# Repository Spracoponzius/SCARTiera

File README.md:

# SCARTiera
Mechanical multiSCART adapter with 6 positions.  

Due to a lack of options of multi-scart adapters ready to buy (always either out of stock, with only three positions or too expensive), i made one myself by reverse engineering a simpler three-positions adapter.  
This is a hobby project, and contributions, suggestions, and feedback are all very welcome.  
This design is currently **untested**, so build this at your own risk.

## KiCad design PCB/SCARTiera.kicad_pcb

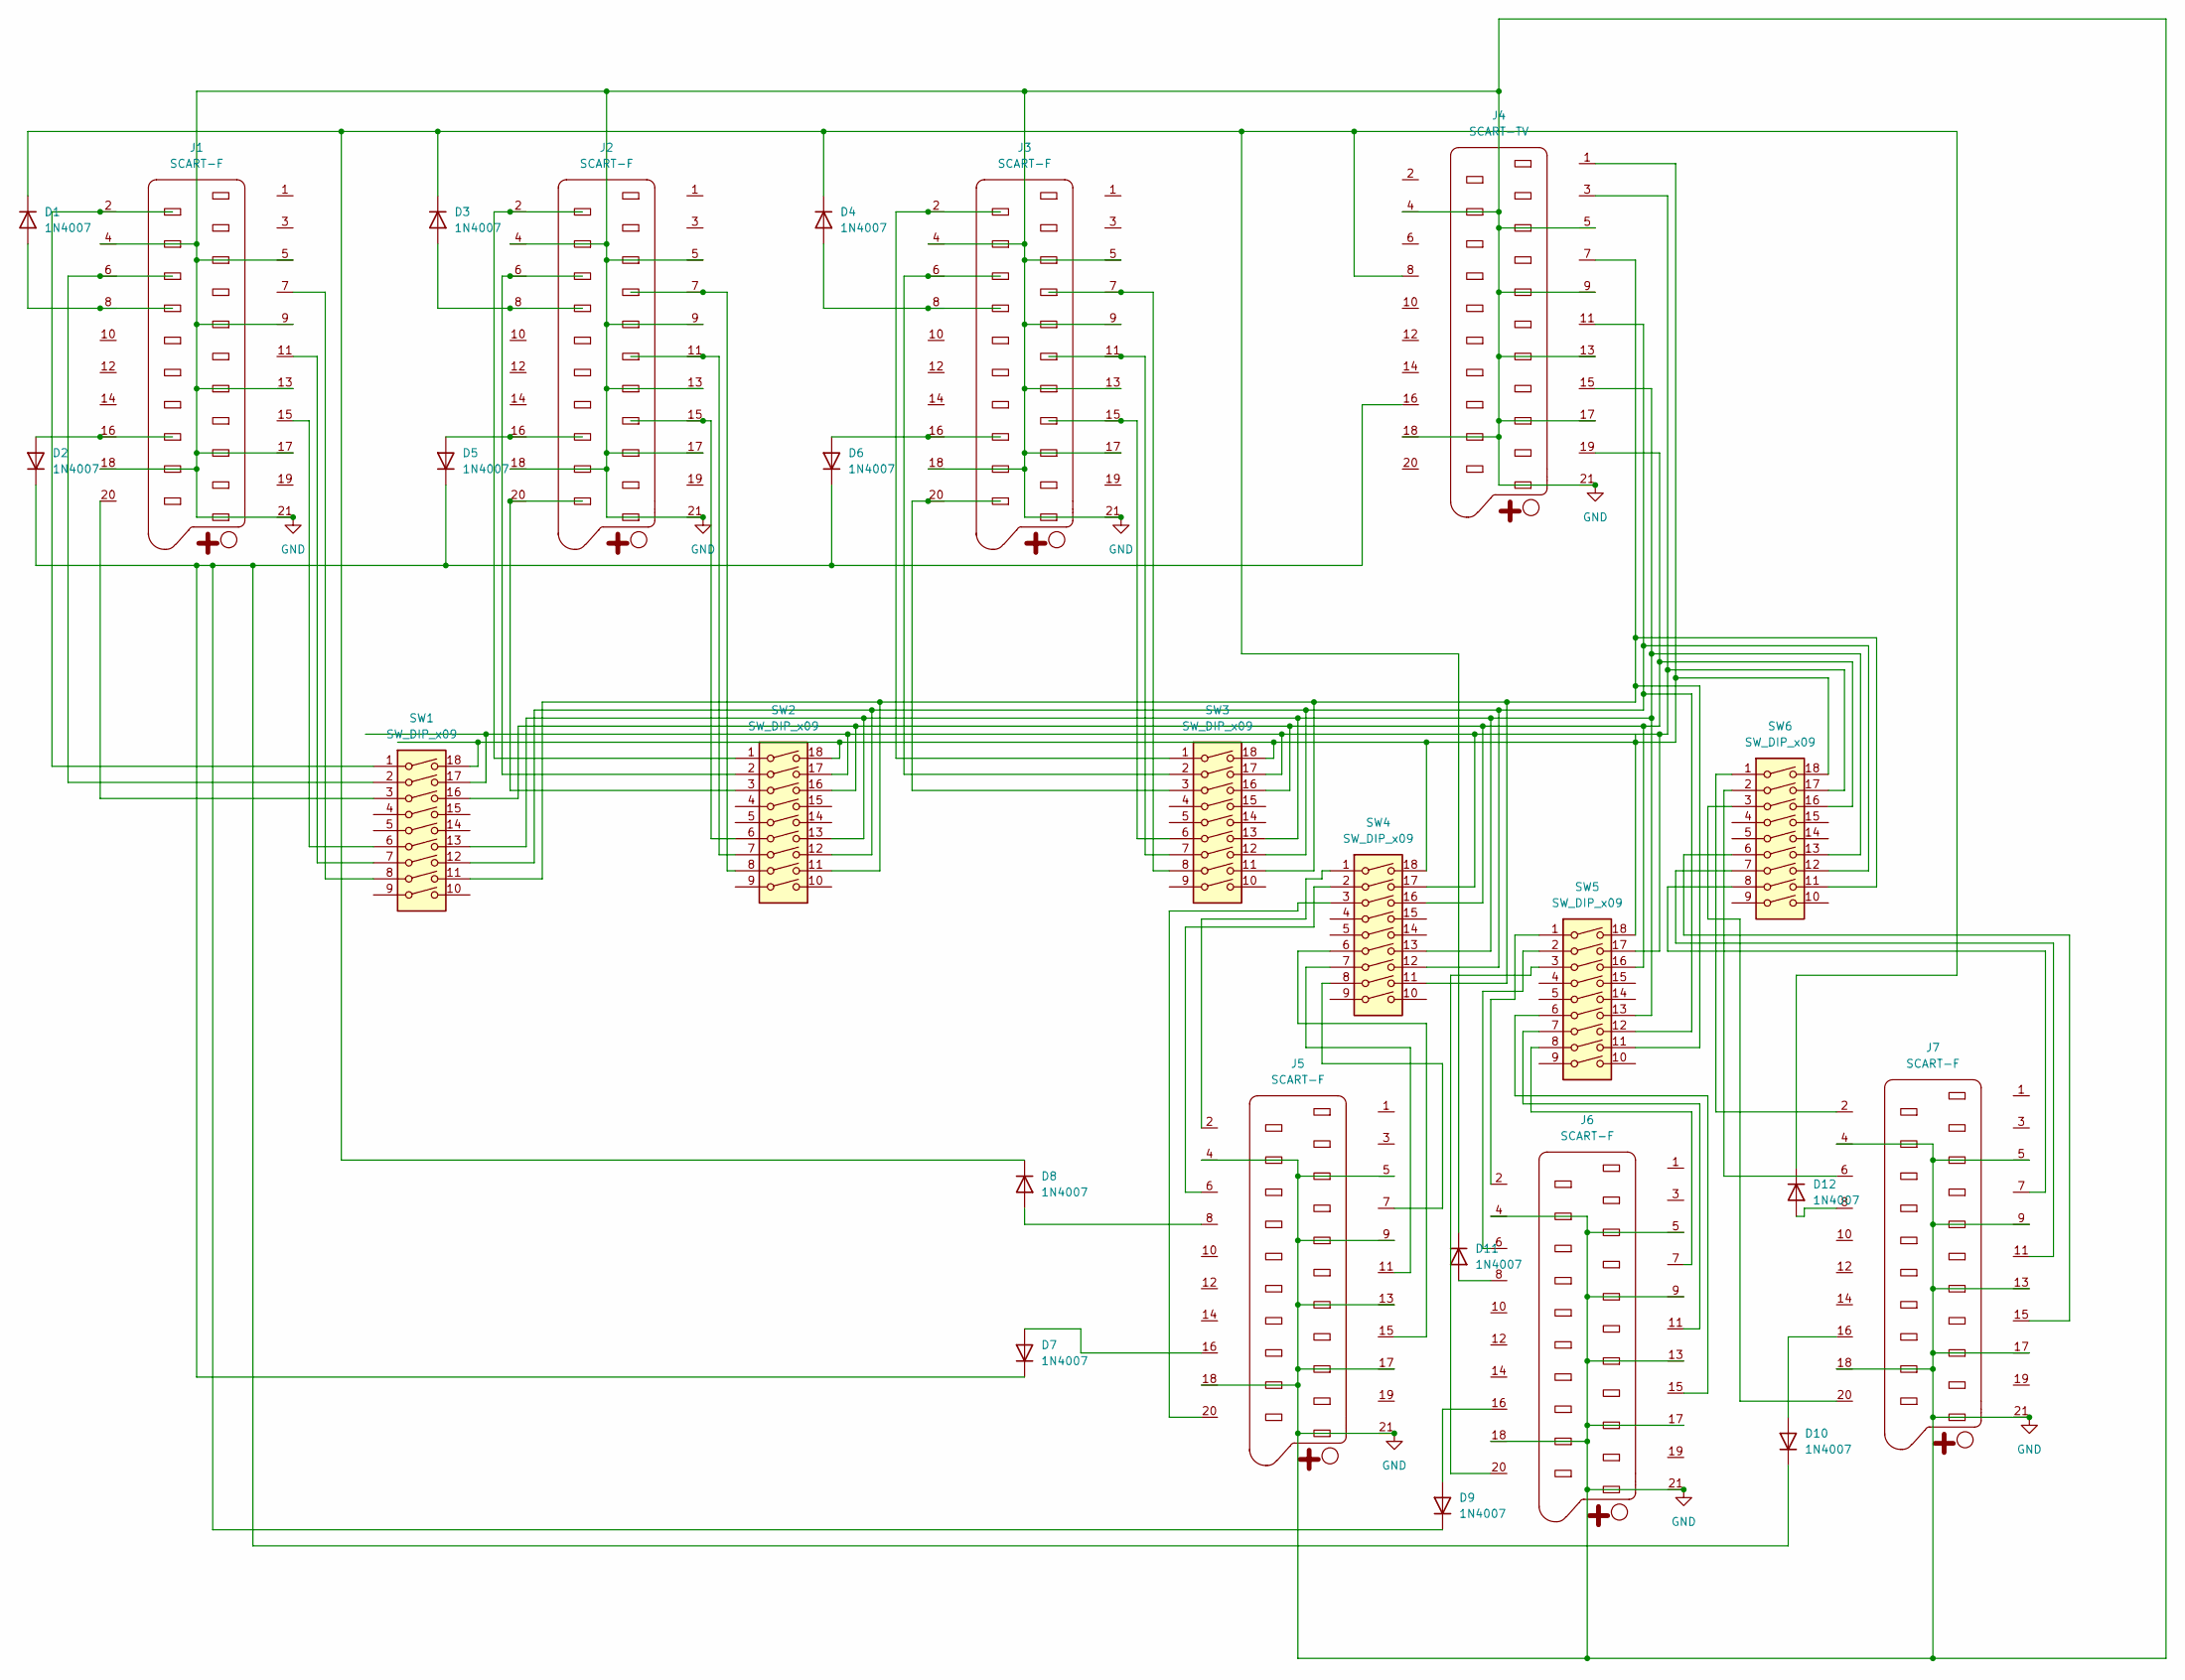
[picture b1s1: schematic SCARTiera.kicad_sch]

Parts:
D1, D2, D3, D4, D5, D6, D7, D8, D9, D10, D11, D12: 1N4007; D_DO-41_SOD81_P10.16mm_Horizontal
J1, J2, J3, J5, J6, J7: SCART-F; SCART_F_Vertical_Wide
J4: SCART-TV; SCART_F_Vertical_Wide
SW1, SW2, SW3, SW4, SW5, SW6: SW_DIP_x09; Switch

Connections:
GND: J1.4, J1.5, J1.9, J1.13, J1.17, J1.18, J1.21, J2.4, J2.5, J2.9, J2.13, J2.17, J2.18, J2.21, J3.4, J3.5, J3.9, J3.13, J3.17, J3.18, J3.21, J4.4, J4.5, J4.9, J4.13, J4.17, J4.18, J4.21, J5.4, J5.5, J5.9, J5.13, J5.17, J5.18, J5.21, J6.4, J6.5, J6.9, J6.13, J6.17, J6.18, J6.21, J7.4, J7.5, J7.9, J7.13, J7.17, J7.18, J7.21
unnamed: D1.2 (A), J1.8
unnamed: D1.1 (K), D3.1 (K), D4.1 (K), D8.1 (K), D11.1 (K), D12.1 (K), J4.8
unnamed: D2.2 (A), J1.16
unnamed: D3.2 (A), J2.8
unnamed: D4.2 (A), J3.8
unnamed: D5.2 (A), J2.16
unnamed: D6.2 (A), J3.16
unnamed: D7.2 (A), J5.16
unnamed: D8.2 (A), J5.8
unnamed: D9.2 (A), J6.16
unnamed: D10.2 (A), J7.16
unnamed: D2.1 (K), D5.1 (K), D6.1 (K), D7.1 (K), D9.1 (K), D10.1 (K), J4.16
unnamed: D11.2 (A), J6.8
unnamed: D12.2 (A), J7.8
unnamed: J1.2, SW1.1
unnamed: J1.6, SW1.2
unnamed: J1.7, SW1.8
unnamed: J1.11, SW1.7
unnamed: J1.15, SW1.6
unnamed: J1.20, SW1.3
unnamed: J2.2, SW2.1
unnamed: J2.6, SW2.2
unnamed: J2.7, SW2.8
unnamed: J2.11, SW2.7
unnamed: J2.15, SW2.6
unnamed: J2.20, SW2.3
unnamed: J3.2, SW3.1
unnamed: J3.6, SW3.2
unnamed: J3.7, SW3.8
unnamed: J3.11, SW3.7
unnamed: J3.15, SW3.6
unnamed: J3.20, SW3.3
unnamed: J4.1, SW1.18, SW2.18, SW3.18, SW4.18, SW5.18, SW6.18
unnamed: J4.3, SW1.17, SW2.17, SW3.17, SW4.17, SW5.17, SW6.17
unnamed: J4.7, SW1.11, SW2.11, SW3.11, SW4.11, SW5.11, SW6.11
unnamed: J4.11, SW1.12, SW2.12, SW3.12, SW4.12, SW5.12, SW6.12
unnamed: J4.15, SW1.13, SW2.13, SW3.13, SW4.13, SW5.13, SW6.13
unnamed: J4.19, SW1.16, SW2.16, SW3.16, SW4.16, SW5.16, SW6.16
unnamed: J5.2, SW4.1
unnamed: J5.6, SW4.2
unnamed: J5.7, SW4.8
unnamed: J5.11, SW4.7
unnamed: J5.15, SW4.6
unnamed: J5.20, SW4.3
unnamed: J6.2, SW5.1
unnamed: J6.6, SW5.2
unnamed: J6.7, SW5.8
unnamed: J6.11, SW5.7
unnamed: J6.15, SW5.6
unnamed: J6.20, SW5.3
unnamed: J7.2, SW6.1
unnamed: J7.6, SW6.2
unnamed: J7.7, SW6.8
unnamed: J7.11, SW6.7
unnamed: J7.15, SW6.6
unnamed: J7.20, SW6.3

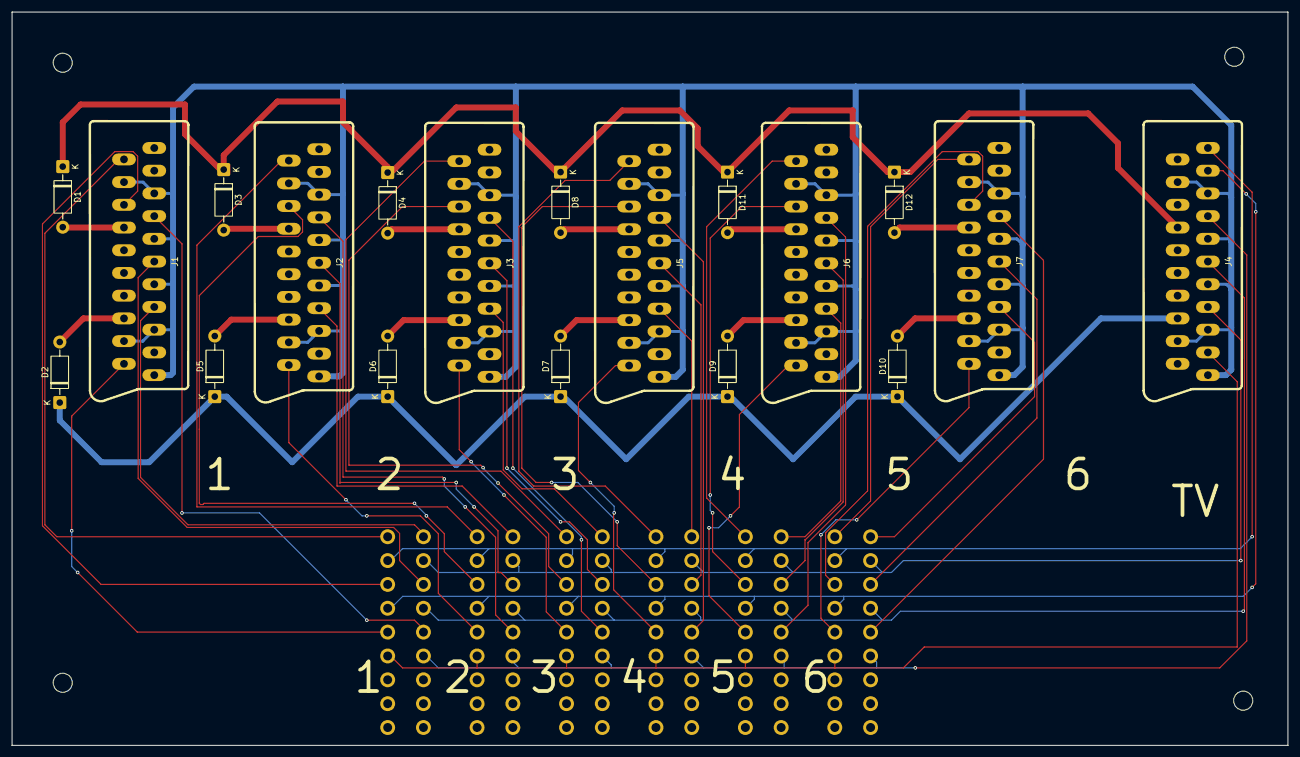
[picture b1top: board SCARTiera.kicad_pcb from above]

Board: 2 copper layers, 214.0 x 123.0 mm, 25 parts (0 on the bottom side), 57 nets.
